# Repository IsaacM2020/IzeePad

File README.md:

# IzeePad 

**IzeePad** is a custom 5-key macropad built as a fun exploration into the world of mechanical keyboards and custom electronics. I spend a lot of time at my desk, and I thought it would be a rewarding challenge to build a tool that makes my creative workflow just a little bit more personal.

---

## 💡 Inspiration & Ideation
The IzeePad started as a "just for fun" project. I wanted to see if I could design something from scratch, from the schematic to the physical 3D-printed case. 

Before this, I had never used **Fusion 360** or **KiCad**, and diving head-first into this build has completely leveled up my skills in 3D modeling and electronics design.

## 🛠 Features
* **5-Key Layout:** Mechanical switches configured as **Programmable Macros**, ready to be mapped to any creative shortcut I need.
* **EC11 Rotary Encoder:** A tactile dial for smooth volume control or timeline scrubbing.
* **0.91" OLED Display:** Visual feedback to show exactly what my pad is doing.
* **Xiao RP2040:** A tiny, powerful "brain" that makes the whole project possible.
* **Custom Build:** Assembled using 3D-printed parts and M3 heatset inserts for a sturdy, professional feel.

---

## 📸 Project Gallery

### Overall Hackpad

*The finished IzeePad: A fun project that adds a personal touch to my desk.*

### Schematic 

*The circuit logic designed in KiCad, showing the wiring for the buttons and OLED.*

### PCB Design

*The custom PCB layout, featuring the Seeed XIAO RP2040 mounted SMD-style.*

### Case & Assembly

*A look at the side profile and the 3D-printed assembly.*

---

## 💻 Firmware Overview
This pad runs on **KMK Firmware** using CircuitPython.
* **The Encoder:** Set to Volume Up/Down with a press-to-mute function.
* **The Keys:** Configured as a **Macro Layer**. Each key is a placeholder ready to be assigned to complex video editing shortcuts or VTuber scene triggers.
* **The Screen:** Provides real-time status updates on active layers.

---

## 📦 BOM (Bill of Materials)
* **1x** Seeed Studio XIAO RP2040
* **5x** MX-Style Mechanical Switches
* **5x** Blank DSA Keycaps (White)
* **1x** EC11 Rotary Encoder
* **1x** 0.91" 128x32 OLED Display (GND-VCC-SCL-SDA)
* **4x** M3x16mm Screws
* **4x** M3x5x4mm Heatset Inserts

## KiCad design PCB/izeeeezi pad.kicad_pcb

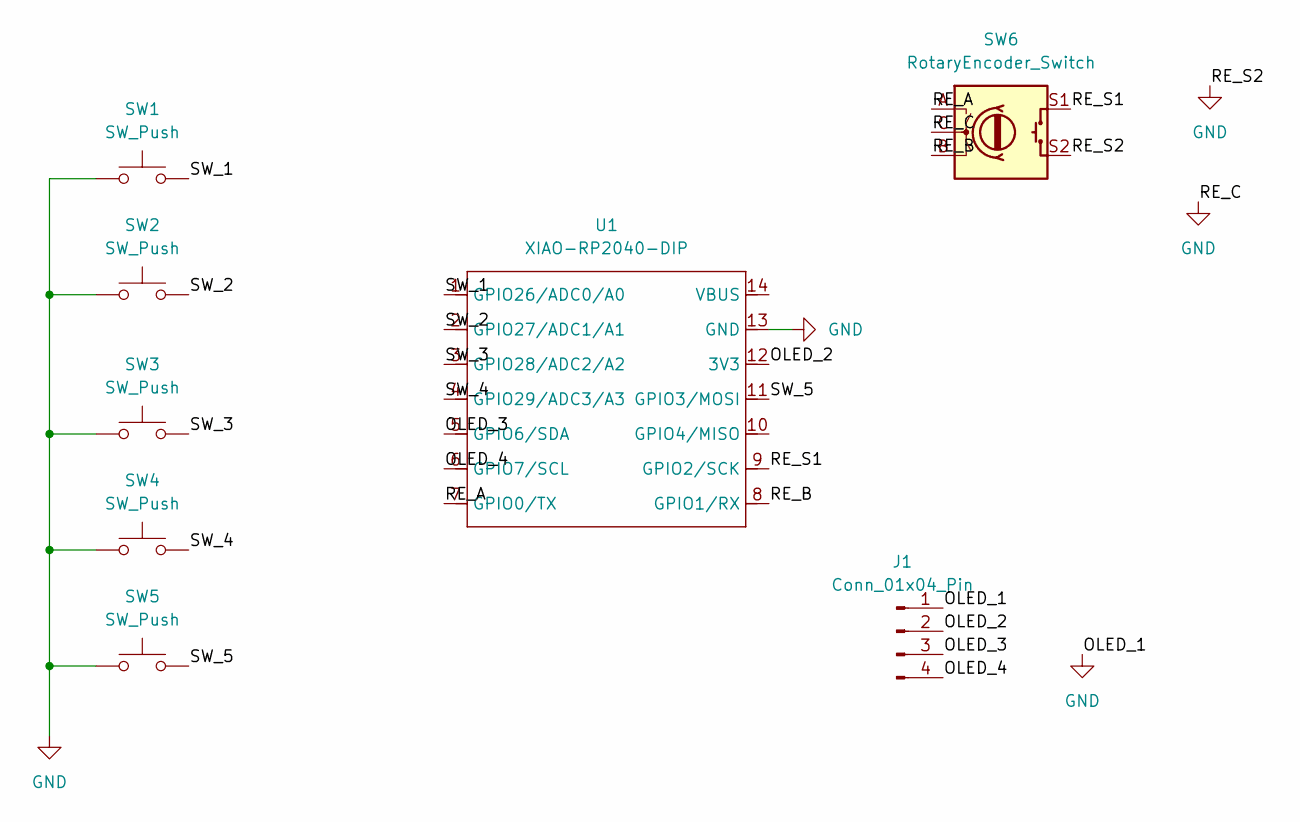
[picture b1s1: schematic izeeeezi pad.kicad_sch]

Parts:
J1: Conn_01x04_Pin; PinHeader_1x04_P2.54mm_Vertical
SW1, SW2, SW3, SW4, SW5: SW_Push; SW_Cherry_MX_1.00u_PCB
SW6: RotaryEncoder_Switch; RotaryEncoder_Alps_EC11E-Switch_Vertical_H20mm
U1: XIAO-RP2040-DIP

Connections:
/OLED_2: J1.2, U1.12 (3V3)
/OLED_3: J1.3, U1.5 (GPIO6/SDA)
/OLED_4: J1.4, U1.6 (GPIO7/SCL)
/RE_A: SW6.A, U1.7 (GPIO0/TX)
/RE_B: SW6.B, U1.8 (GPIO1/RX)
/RE_S1: SW6.S1, U1.9 (GPIO2/SCK)
/SW_1: SW1.2, U1.1 (GPIO26/ADC0/A0)
/SW_2: SW2.2, U1.2 (GPIO27/ADC1/A1)
/SW_3: SW3.2, U1.3 (GPIO28/ADC2/A2)
/SW_4: SW4.2, U1.4 (GPIO29/ADC3/A3)
/SW_5: SW5.2, U1.11 (GPIO3/MOSI)
GND: J1.1, SW1.1, SW2.1, SW3.1, SW4.1, SW5.1, SW6.C, SW6.S2, U1.13 (GND)

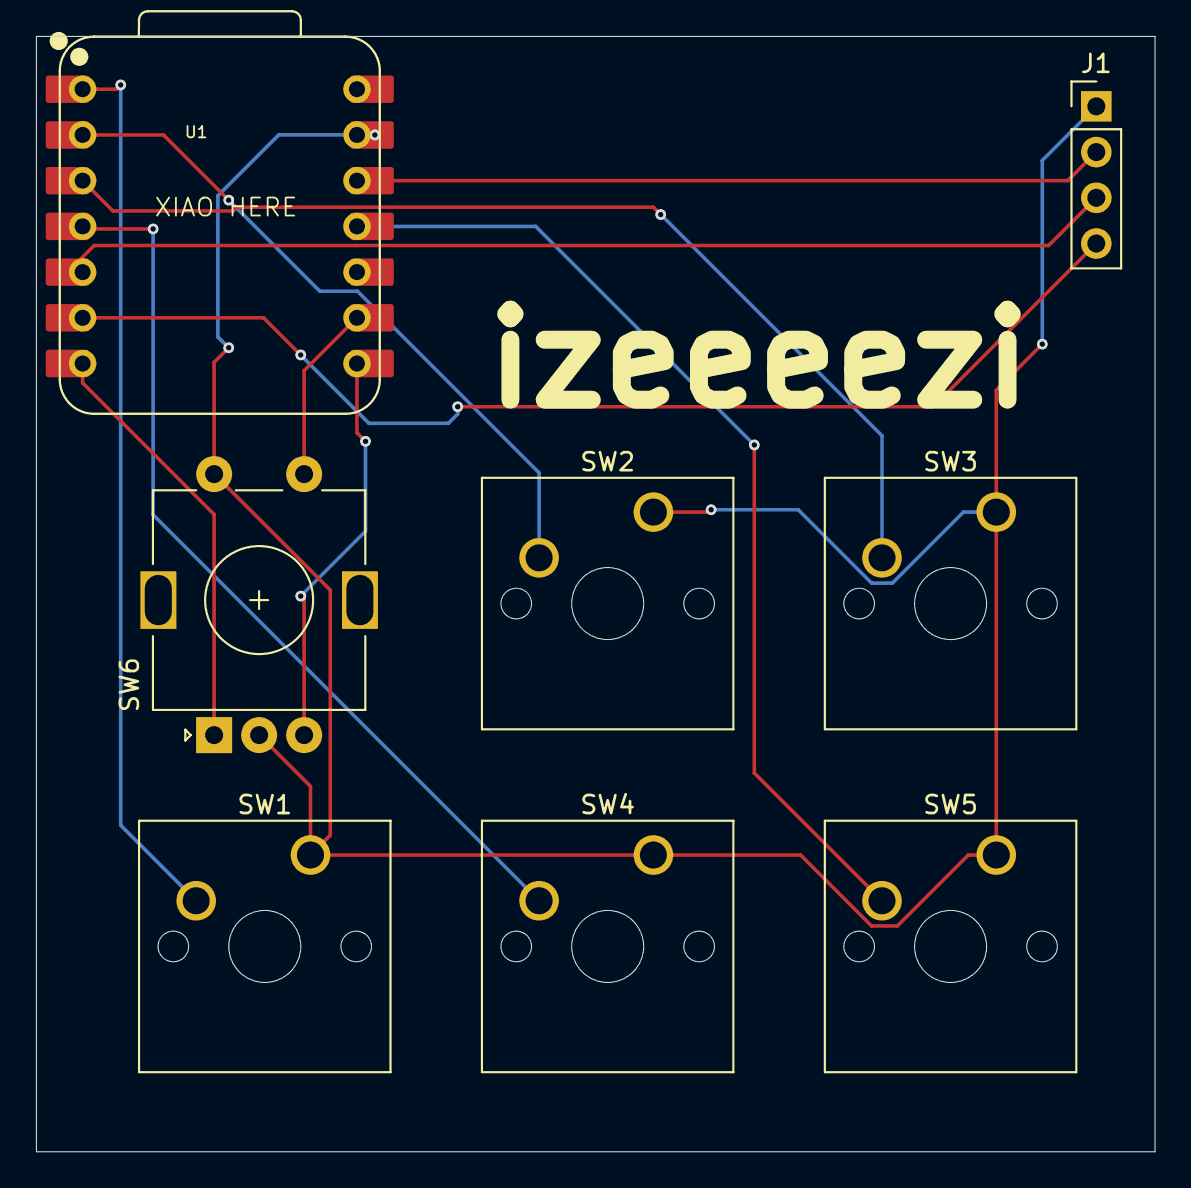
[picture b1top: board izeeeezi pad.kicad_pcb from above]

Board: 2 copper layers, 62.1 x 62.0 mm, 8 parts (0 on the bottom side), 12 nets.

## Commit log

2026-01-19 rendered file
2026-01-19 updated for the rendered file
